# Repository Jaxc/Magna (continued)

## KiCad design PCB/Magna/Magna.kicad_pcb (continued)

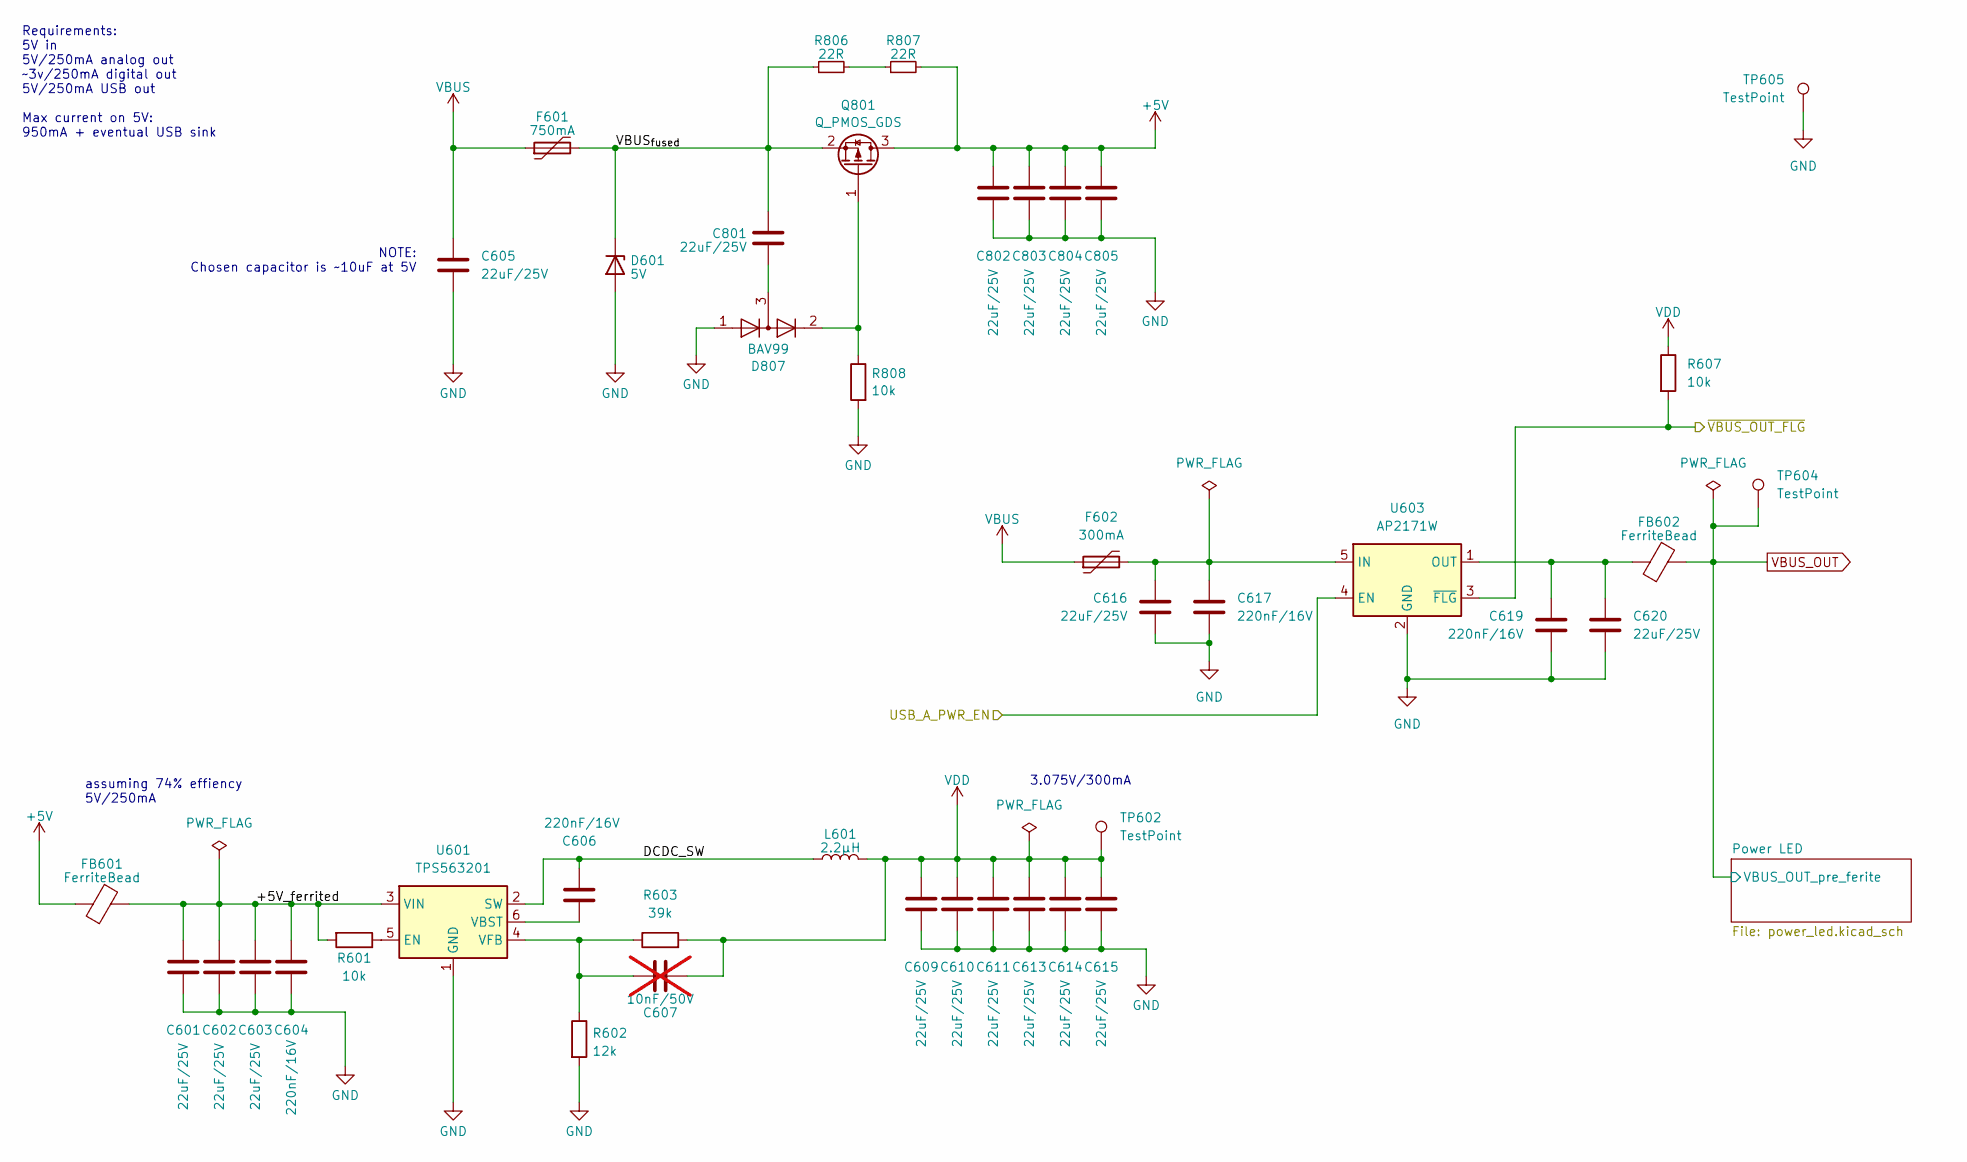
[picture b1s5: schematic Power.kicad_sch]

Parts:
C601, C602, C603, C605, C609, C610, C611, C613, C614, C615, C616, C620, C801, C802, C803, C804, C805: 22uF/25V; C_0805_2012Metric_Pad1.18x1.45mm_HandSolder; LCSC C45783
C604, C606, C617, C619: 220nF/16V; C_0402_1005Metric_Pad0.74x0.62mm_HandSolder; LCSC C16772
C607: 10nF/50V; C_0805_2012Metric_Pad1.18x1.45mm_HandSolder; LCSC C1710; not fitted
D601: 5V; D_SOD-123; LCSC C19077393
D807: BAV99; SOT-23; LCSC C2500
F601: 750mA; Fuse_2920_7451Metric_Pad2.10x5.45mm_HandSolder; LCSC C20822
F602: 300mA; Fuse_2920_7451Metric_Pad2.10x5.45mm_HandSolder; LCSC C20820
FB601, FB602: FerriteBead; L_0805_2012Metric; LCSC C1015
L601: 2.2µH; L_Sunlord_SWPA3012S; LCSC C182126
Q801: Q_PMOS_GDS; SOT-23; LCSC C15127
R601, R607, R808: 10k; R_0805_2012Metric_Pad1.20x1.40mm_HandSolder; LCSC C17414
R602: 12k; R_0805_2012Metric_Pad1.20x1.40mm_HandSolder; LCSC C17444
R603: 39k; R_0805_2012Metric_Pad1.20x1.40mm_HandSolder; LCSC C17713
R806, R807: 22R; R_0805_2012Metric_Pad1.20x1.40mm_HandSolder; LCSC C17561
TP602, TP604, TP605: TestPoint; TestPoint_Keystone_5000-5004_Miniature
U601: TPS563201; SOT-23-6; LCSC C116592
U603: AP2171W; SOT-23-5; LCSC C110466

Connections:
+5V: C802.1, C803.1, C804.1, C805.1, FB601.1, Q801.3 (D), R807.2; also elsewhere on the board
/MCU/USB_A_PWR_EN: U603.4 (EN); also elsewhere on the board
/MCU/~VBUS_OUT_FLG: R607.2, U603.3 (~FLG); also elsewhere on the board
/POWER/+5V_ferrited: C601.1, C602.1, C603.1, C604.1, FB601.2, R601.2, U601.3 (VIN)
/POWER/DCDC_SW: C606.1, L601.1, U601.2 (SW)
/POWER/VBUS_{fused}: C801.1, D601.1 (K), F601.2, Q801.2 (S), R806.1
GND: C601.2, C602.2, C603.2, C604.2, C605.2, C609.2, C610.2, C611.2, C613.2, C614.2, C615.2, C616.2, C617.2, C619.2, C620.2, C802.2, C803.2, C804.2, C805.2, D601.2 (A), D807.1 (K), R602.2, R808.2, TP605.1, U601.1 (GND), U603.2 (GND); also elsewhere on the board
unnamed: C801.2, D807.3 (K)
unnamed: D807.2 (A), Q801.1 (G), R808.1
unnamed: R806.2, R807.1
unnamed: R601.1, U601.5 (EN)
unnamed: C606.2, U601.6 (VBST)
unnamed: C607.1, R602.1, R603.1, U601.4 (VFB)
unnamed: C616.1, C617.1, F602.2, U603.5 (IN)
unnamed: C619.1, C620.1, FB602.1, U603.1 (OUT)
VBUS: C605.1, F601.1, F602.1; also elsewhere on the board
VBUS_OUT: FB602.2, TP604.1; also elsewhere on the board
VDD: C607.2, C609.1, C610.1, C611.1, C613.1, C614.1, C615.1, L601.2, R603.2, R607.1, TP602.1; also elsewhere on the board

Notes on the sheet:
NOTE: Chosen capacitor is ~10uF at 5V
3.075V/300mA
assuming 74% effiency 5V/250mA
Requirements: 5V in 5V/250mA analog out ~3v/250mA digital out 5V/250mA USB out Max current on 5V: 950mA + eventual USB sink

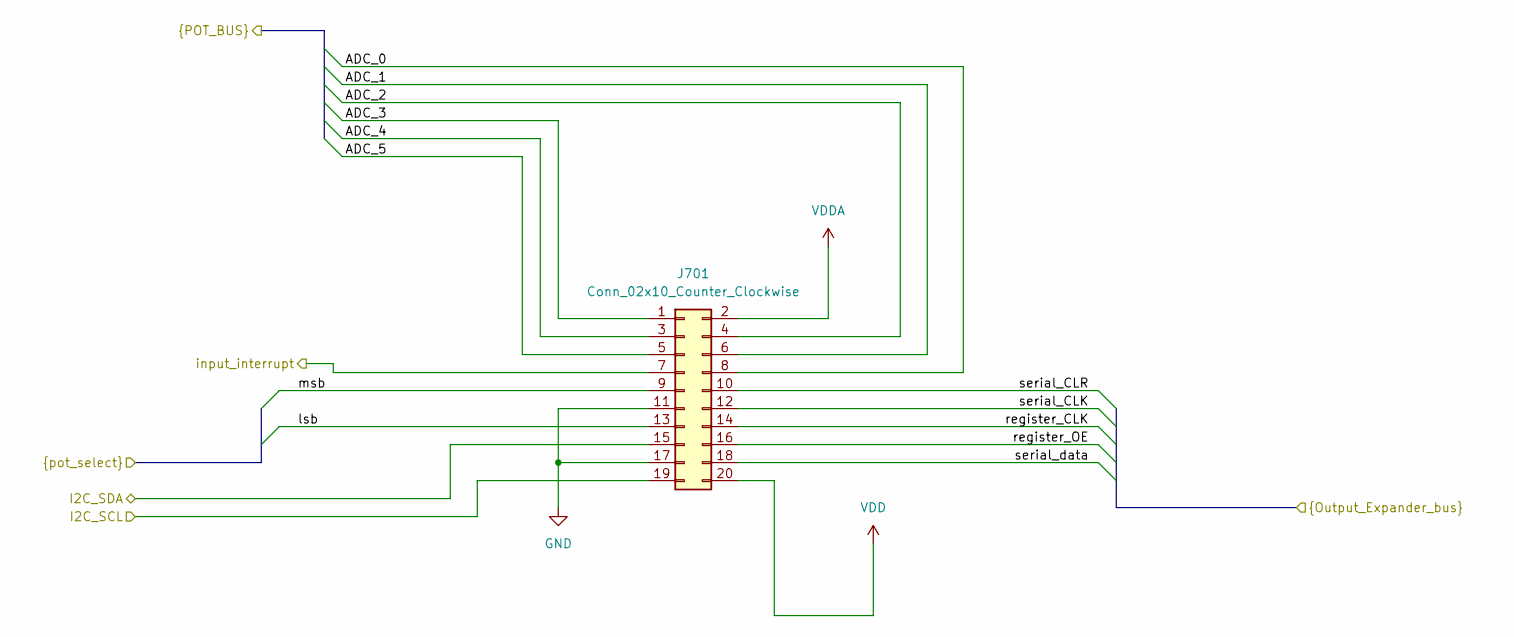
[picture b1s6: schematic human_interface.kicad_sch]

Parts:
J701: Conn_02x10_Counter_Clockwise; PinHeader_2x10_P2.54mm_Horizontal

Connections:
/Human Interface/ADC_0: J701.8; also elsewhere on the board
/Human Interface/ADC_1: J701.6; also elsewhere on the board
/Human Interface/ADC_2: J701.4; also elsewhere on the board
/Human Interface/ADC_3: J701.1; also elsewhere on the board
/Human Interface/ADC_4: J701.3; also elsewhere on the board
/Human Interface/ADC_5: J701.5; also elsewhere on the board
/Human Interface/I2C_SCL: J701.19; also elsewhere on the board
/Human Interface/I2C_SDA: J701.15; also elsewhere on the board
/Human Interface/input_interrupt: J701.7; also elsewhere on the board
/Human Interface/lsb: J701.13; also elsewhere on the board
/Human Interface/msb: J701.9; also elsewhere on the board
/Human Interface/register_CLK: J701.14; also elsewhere on the board
/Human Interface/register_OE: J701.16; also elsewhere on the board
/Human Interface/serial_CLK: J701.12; also elsewhere on the board
/Human Interface/serial_CLR: J701.10; also elsewhere on the board
/Human Interface/serial_data: J701.18; also elsewhere on the board
GND: J701.11, J701.17; also elsewhere on the board
VDD: J701.20; also elsewhere on the board
VDDA: J701.2; also elsewhere on the board

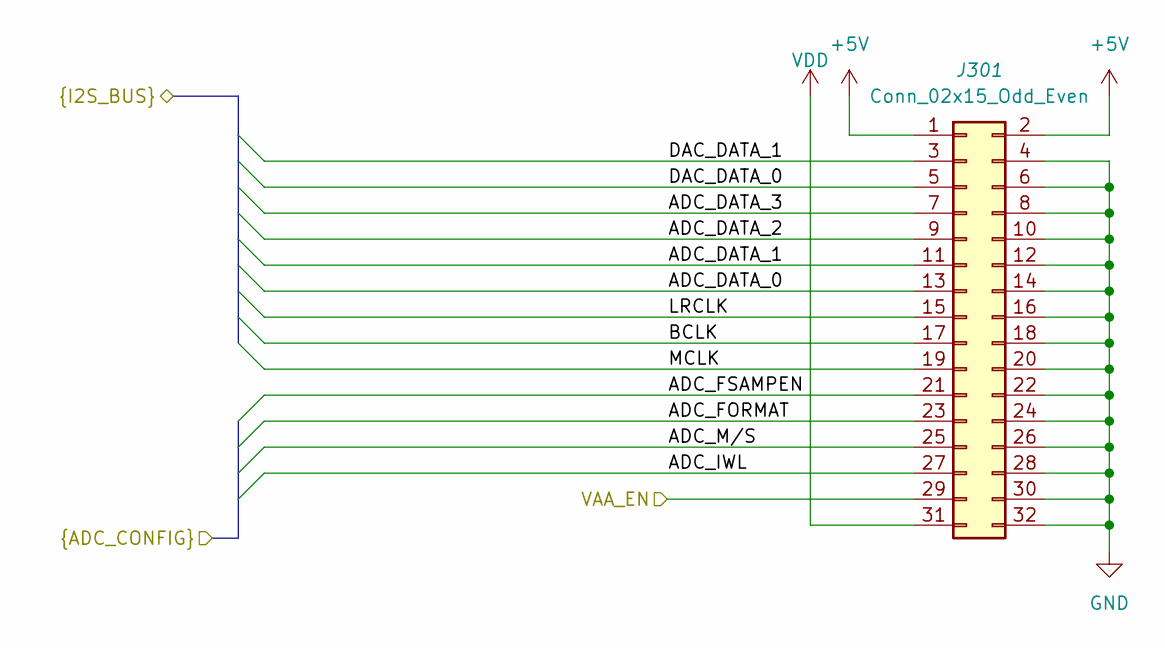
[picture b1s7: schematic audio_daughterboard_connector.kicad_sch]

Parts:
J301: Conn_02x15_Odd_Even; PinSocket_2x16_P2.54mm_Horizontal

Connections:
+5V: J301.1, J301.2; also elsewhere on the board
/Audio Daughterboard Connector/ADC_DATA_0: J301.13; also elsewhere on the board
/Audio Daughterboard Connector/ADC_DATA_1: J301.11; also elsewhere on the board
/Audio Daughterboard Connector/ADC_DATA_2: J301.9; also elsewhere on the board
/Audio Daughterboard Connector/ADC_DATA_3: J301.7; also elsewhere on the board
/Audio Daughterboard Connector/ADC_FORMAT: J301.23; also elsewhere on the board
/Audio Daughterboard Connector/ADC_FSAMPEN: J301.21; also elsewhere on the board
/Audio Daughterboard Connector/ADC_IWL: J301.27; also elsewhere on the board
/Audio Daughterboard Connector/ADC_M/S: J301.25; also elsewhere on the board
/Audio Daughterboard Connector/BCLK: J301.17; also elsewhere on the board
/Audio Daughterboard Connector/DAC_DATA_0: J301.5; also elsewhere on the board
/Audio Daughterboard Connector/DAC_DATA_1: J301.3; also elsewhere on the board
/Audio Daughterboard Connector/LRCLK: J301.15; also elsewhere on the board
/Audio Daughterboard Connector/MCLK: J301.19; also elsewhere on the board
/Audio Daughterboard Connector/VAA_EN: J301.29; also elsewhere on the board
GND: J301.4, J301.6, J301.8, J301.10, J301.12, J301.14, J301.16, J301.18, J301.20, J301.22, J301.24, J301.26, J301.28, J301.30, J301.32; also elsewhere on the board
VDD: J301.31; also elsewhere on the board

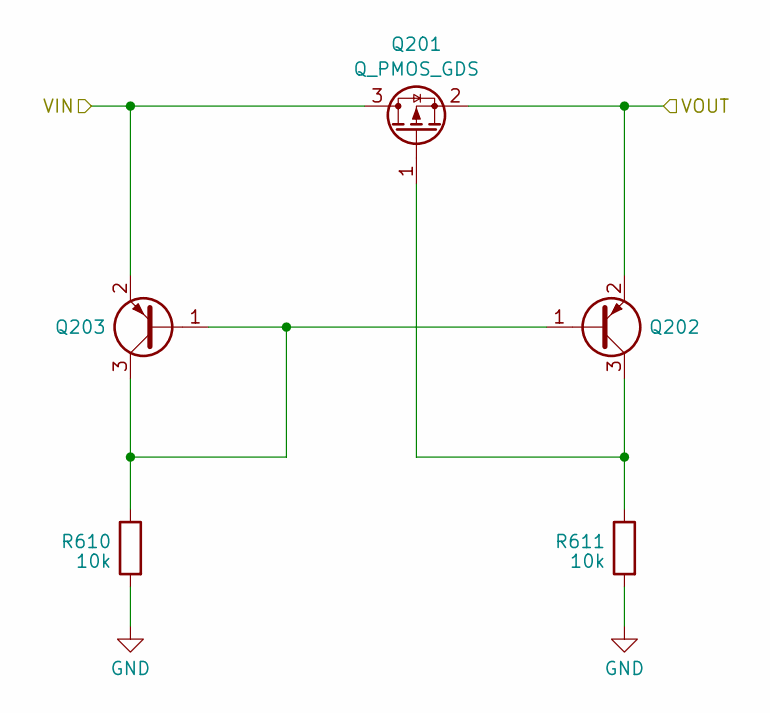
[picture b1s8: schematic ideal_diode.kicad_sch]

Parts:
Q201: Q_PMOS_GDS; SOT-23; LCSC C15127
Q202, Q203: Q_PNP_BEC; SOT-23; LCSC C8326
R610, R611: 10k; R_0805_2012Metric_Pad1.20x1.40mm_HandSolder; LCSC C17414

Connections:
/USB/USB_B_VBUS: Q201.3 (D), Q203.2 (E); also elsewhere on the board
GND: R610.2, R611.2; also elsewhere on the board
unnamed: Q201.1 (G), Q202.3 (C), R611.1
unnamed: Q202.1 (B), Q203.1 (B), Q203.3 (C), R610.1
VBUS: Q201.2 (S), Q202.2 (E); also elsewhere on the board

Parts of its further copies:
Q701: Q_PMOS_GDS; SOT-23; LCSC C15127
Q702, Q703: Q_PNP_BEC; SOT-23; LCSC C8326
R608, R609: 10k; R_0805_2012Metric_Pad1.20x1.40mm_HandSolder; LCSC C17414

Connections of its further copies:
/USB/USB_C_VBUS: Q701.3 (D), Q703.2 (E); also elsewhere on the board
GND: R608.2, R609.2; also elsewhere on the board
unnamed: Q701.1 (G), Q702.3 (C), R609.1
unnamed: Q702.1 (B), Q703.1 (B), Q703.3 (C), R608.1
VBUS: Q701.2 (S), Q702.2 (E); also elsewhere on the board

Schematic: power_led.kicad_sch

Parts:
D801, D802, D803, D804, D805: Red; D_0805_2012Metric_Pad1.15x1.40mm_HandSolder; LCSC C84256
R801, R802, R803: 680R; R_0805_2012Metric_Pad1.20x1.40mm_HandSolder; LCSC C17798
R804, R805: 220R; R_0805_2012Metric_Pad1.20x1.40mm_HandSolder; LCSC C17557

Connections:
+5V: R803.1; also elsewhere on the board
GND: D801.1 (K), D802.1 (K), D803.1 (K), D804.1 (K), D805.1 (K); also elsewhere on the board
unnamed: D801.2 (A), R801.2
unnamed: D802.2 (A), R802.2
unnamed: D803.2 (A), R803.2
unnamed: D804.2 (A), R804.2
unnamed: D805.2 (A), R805.2
VBUS: R802.1; also elsewhere on the board
VBUS_OUT: R801.1; also elsewhere on the board
VDD: R804.1; also elsewhere on the board
VDDA: R805.1; also elsewhere on the board

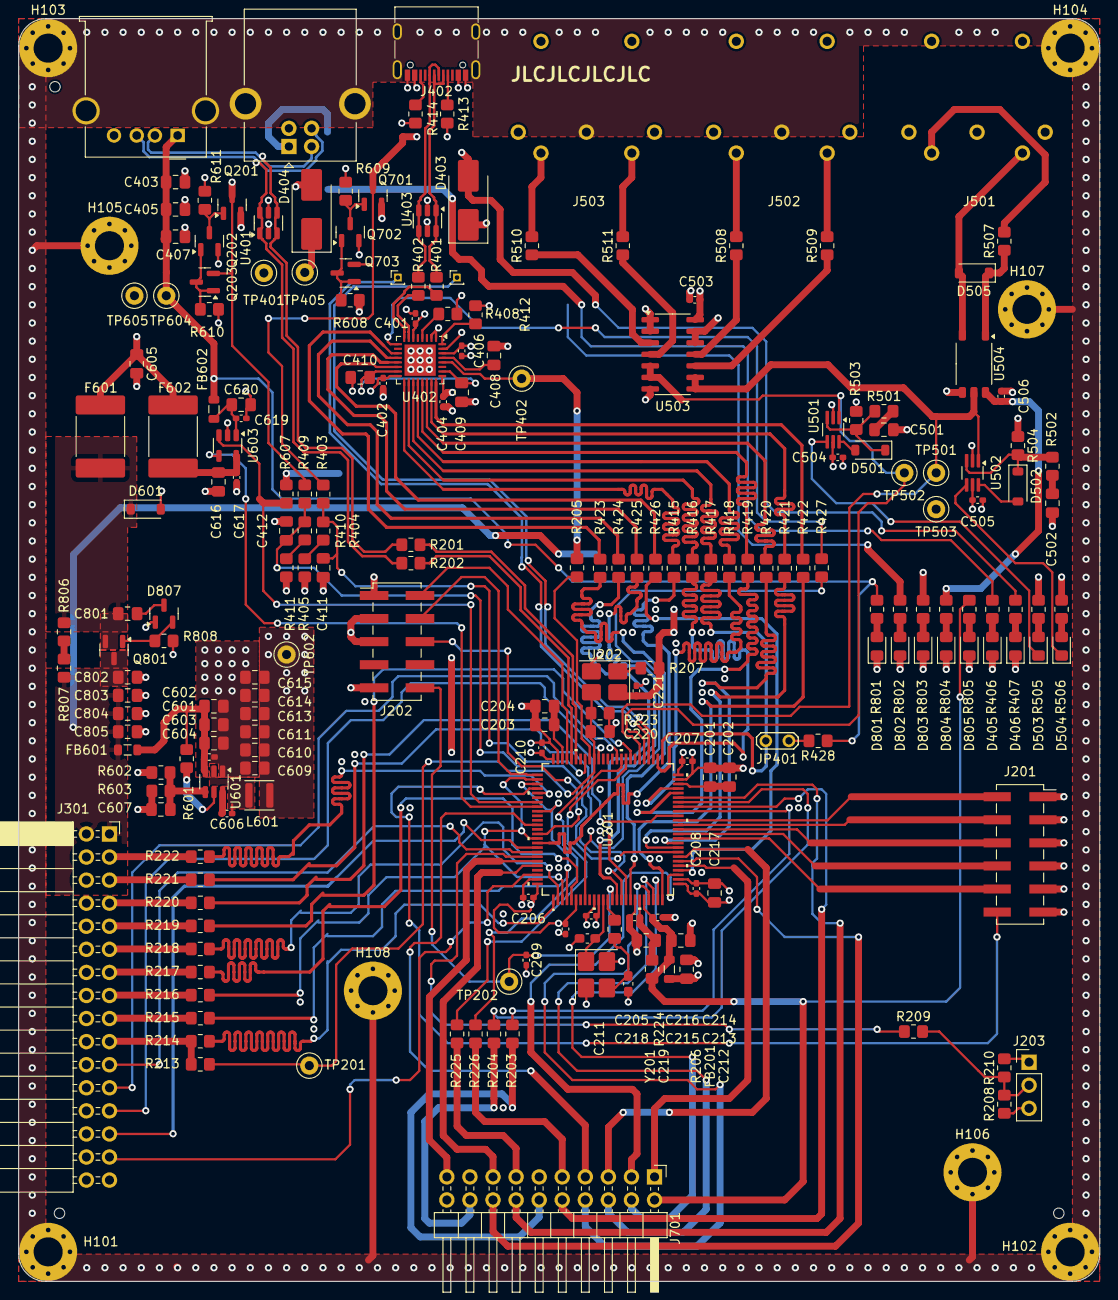
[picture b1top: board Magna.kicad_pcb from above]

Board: 4 copper layers, 119.0 x 139.0 mm, 217 parts (0 on the bottom side), 168 nets.

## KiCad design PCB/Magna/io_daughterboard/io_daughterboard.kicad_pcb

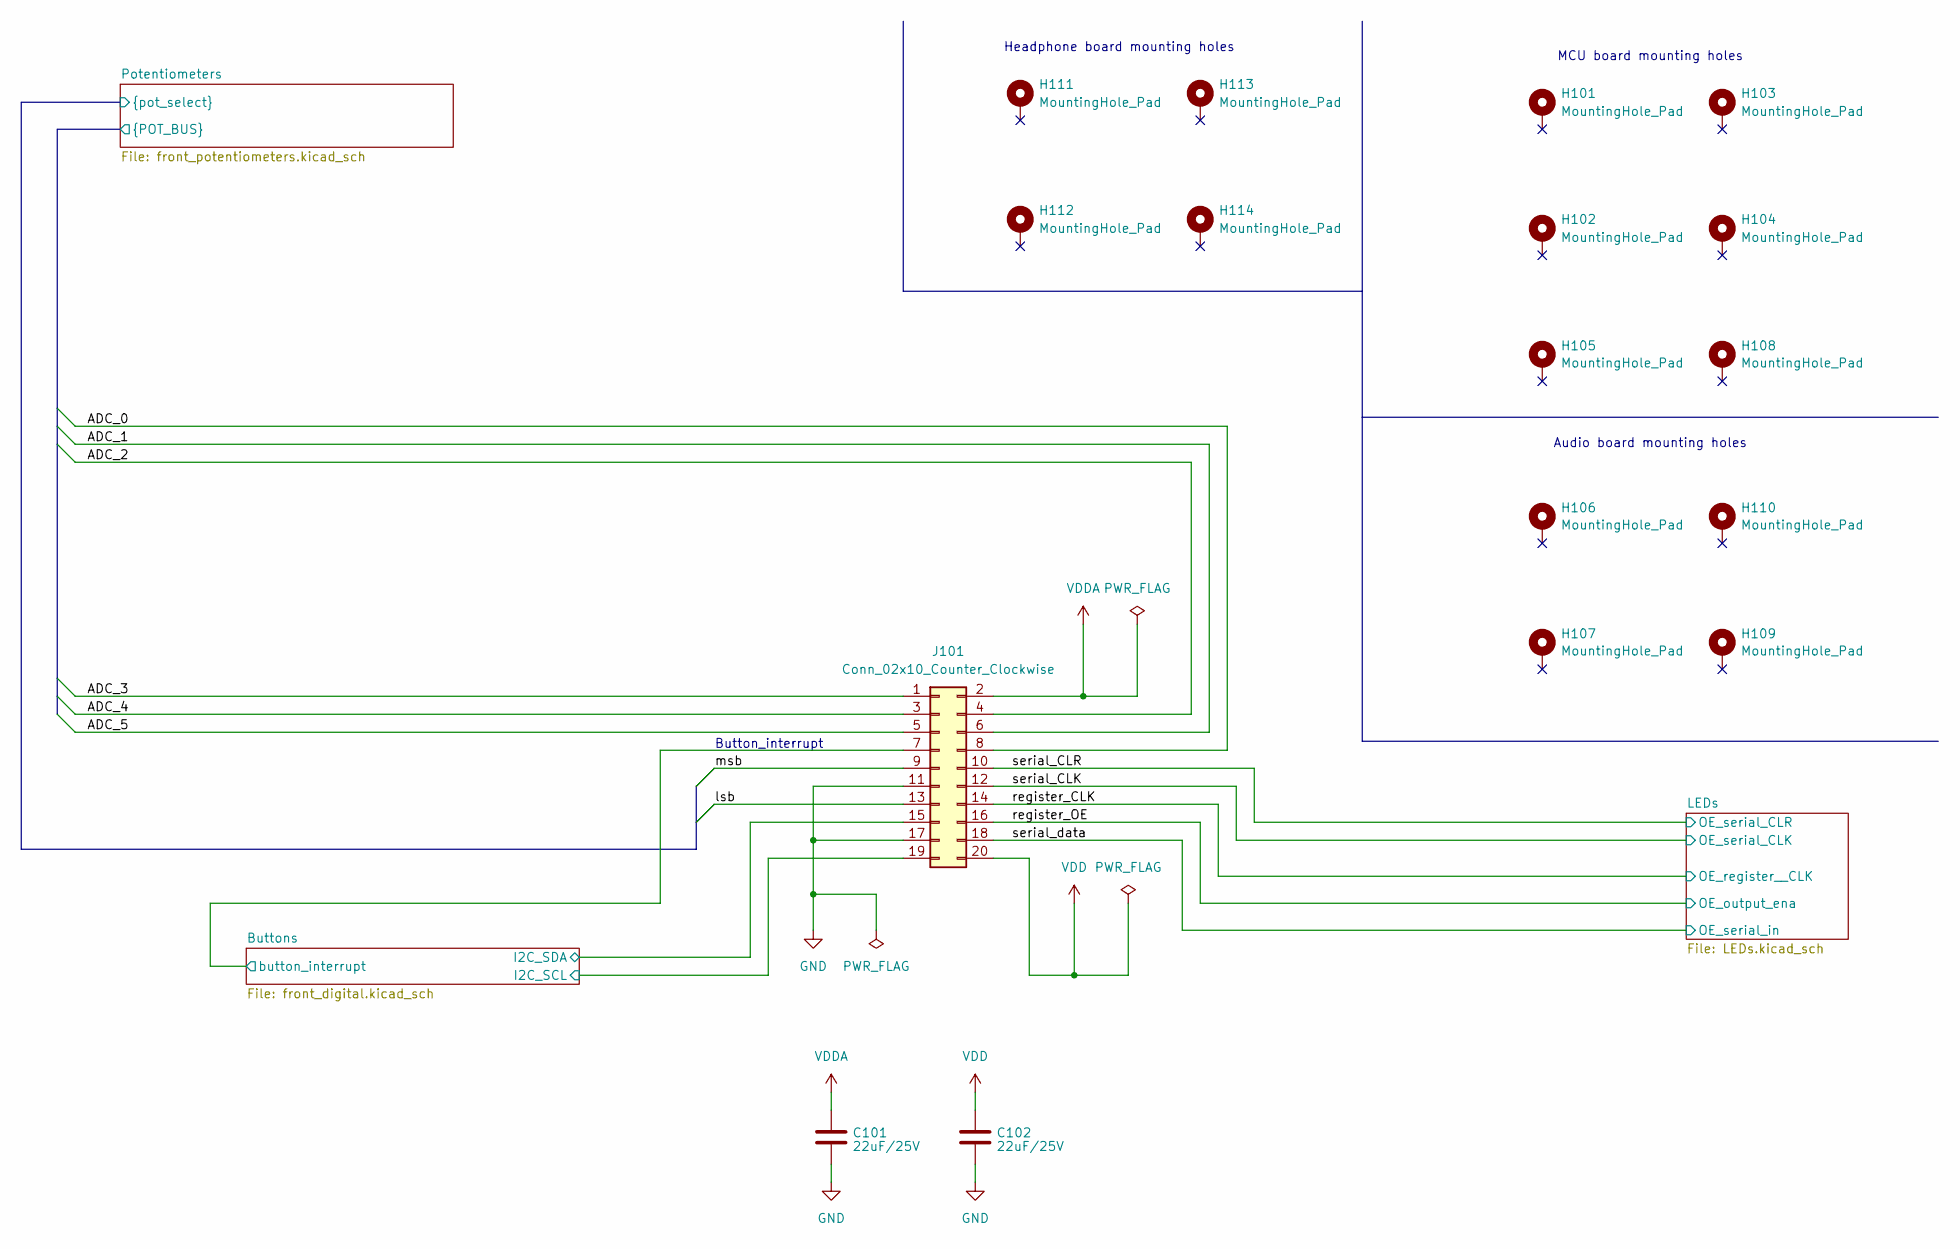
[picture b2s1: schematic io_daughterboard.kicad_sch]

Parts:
C101, C102: 22uF/25V; C_0805_2012Metric_Pad1.18x1.45mm_HandSolder; LCSC C45783
H101, H102, H103, H104, H105, H106, H107, H108, H109, H110, H111, H112, H113, H114: MountingHole_Pad; MountingHole_3.2mm_M3_Pad_Via
J101: Conn_02x10_Counter_Clockwise; PinSocket_2x10_P2.54mm_Vertical

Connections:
/Buttons/I2C_SCL: J101.19; also elsewhere on the board
/Buttons/I2C_SDA: J101.15; also elsewhere on the board
/Buttons/button_interrupt: J101.7; also elsewhere on the board
/Potentiometers/ADC_0: J101.8; also elsewhere on the board
/Potentiometers/ADC_1: J101.6; also elsewhere on the board
/Potentiometers/ADC_2: J101.4; also elsewhere on the board
/Potentiometers/ADC_3: J101.1; also elsewhere on the board
/Potentiometers/ADC_4: J101.3; also elsewhere on the board
/Potentiometers/ADC_5: J101.5; also elsewhere on the board
/Potentiometers/lsb: J101.13; also elsewhere on the board
/Potentiometers/msb: J101.9; also elsewhere on the board
/register_CLK: J101.14; also elsewhere on the board
/register_OE: J101.16; also elsewhere on the board
/serial_CLK: J101.12; also elsewhere on the board
/serial_CLR: J101.10; also elsewhere on the board
/serial_data: J101.18; also elsewhere on the board
GND: C101.2, C102.2, J101.11, J101.17; also elsewhere on the board
VDD: C102.1, J101.20; also elsewhere on the board
VDDA: C101.1, J101.2; also elsewhere on the board

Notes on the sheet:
Audio board mounting holes
MCU board mounting holes
Button_interrupt
Headphone board mounting holes

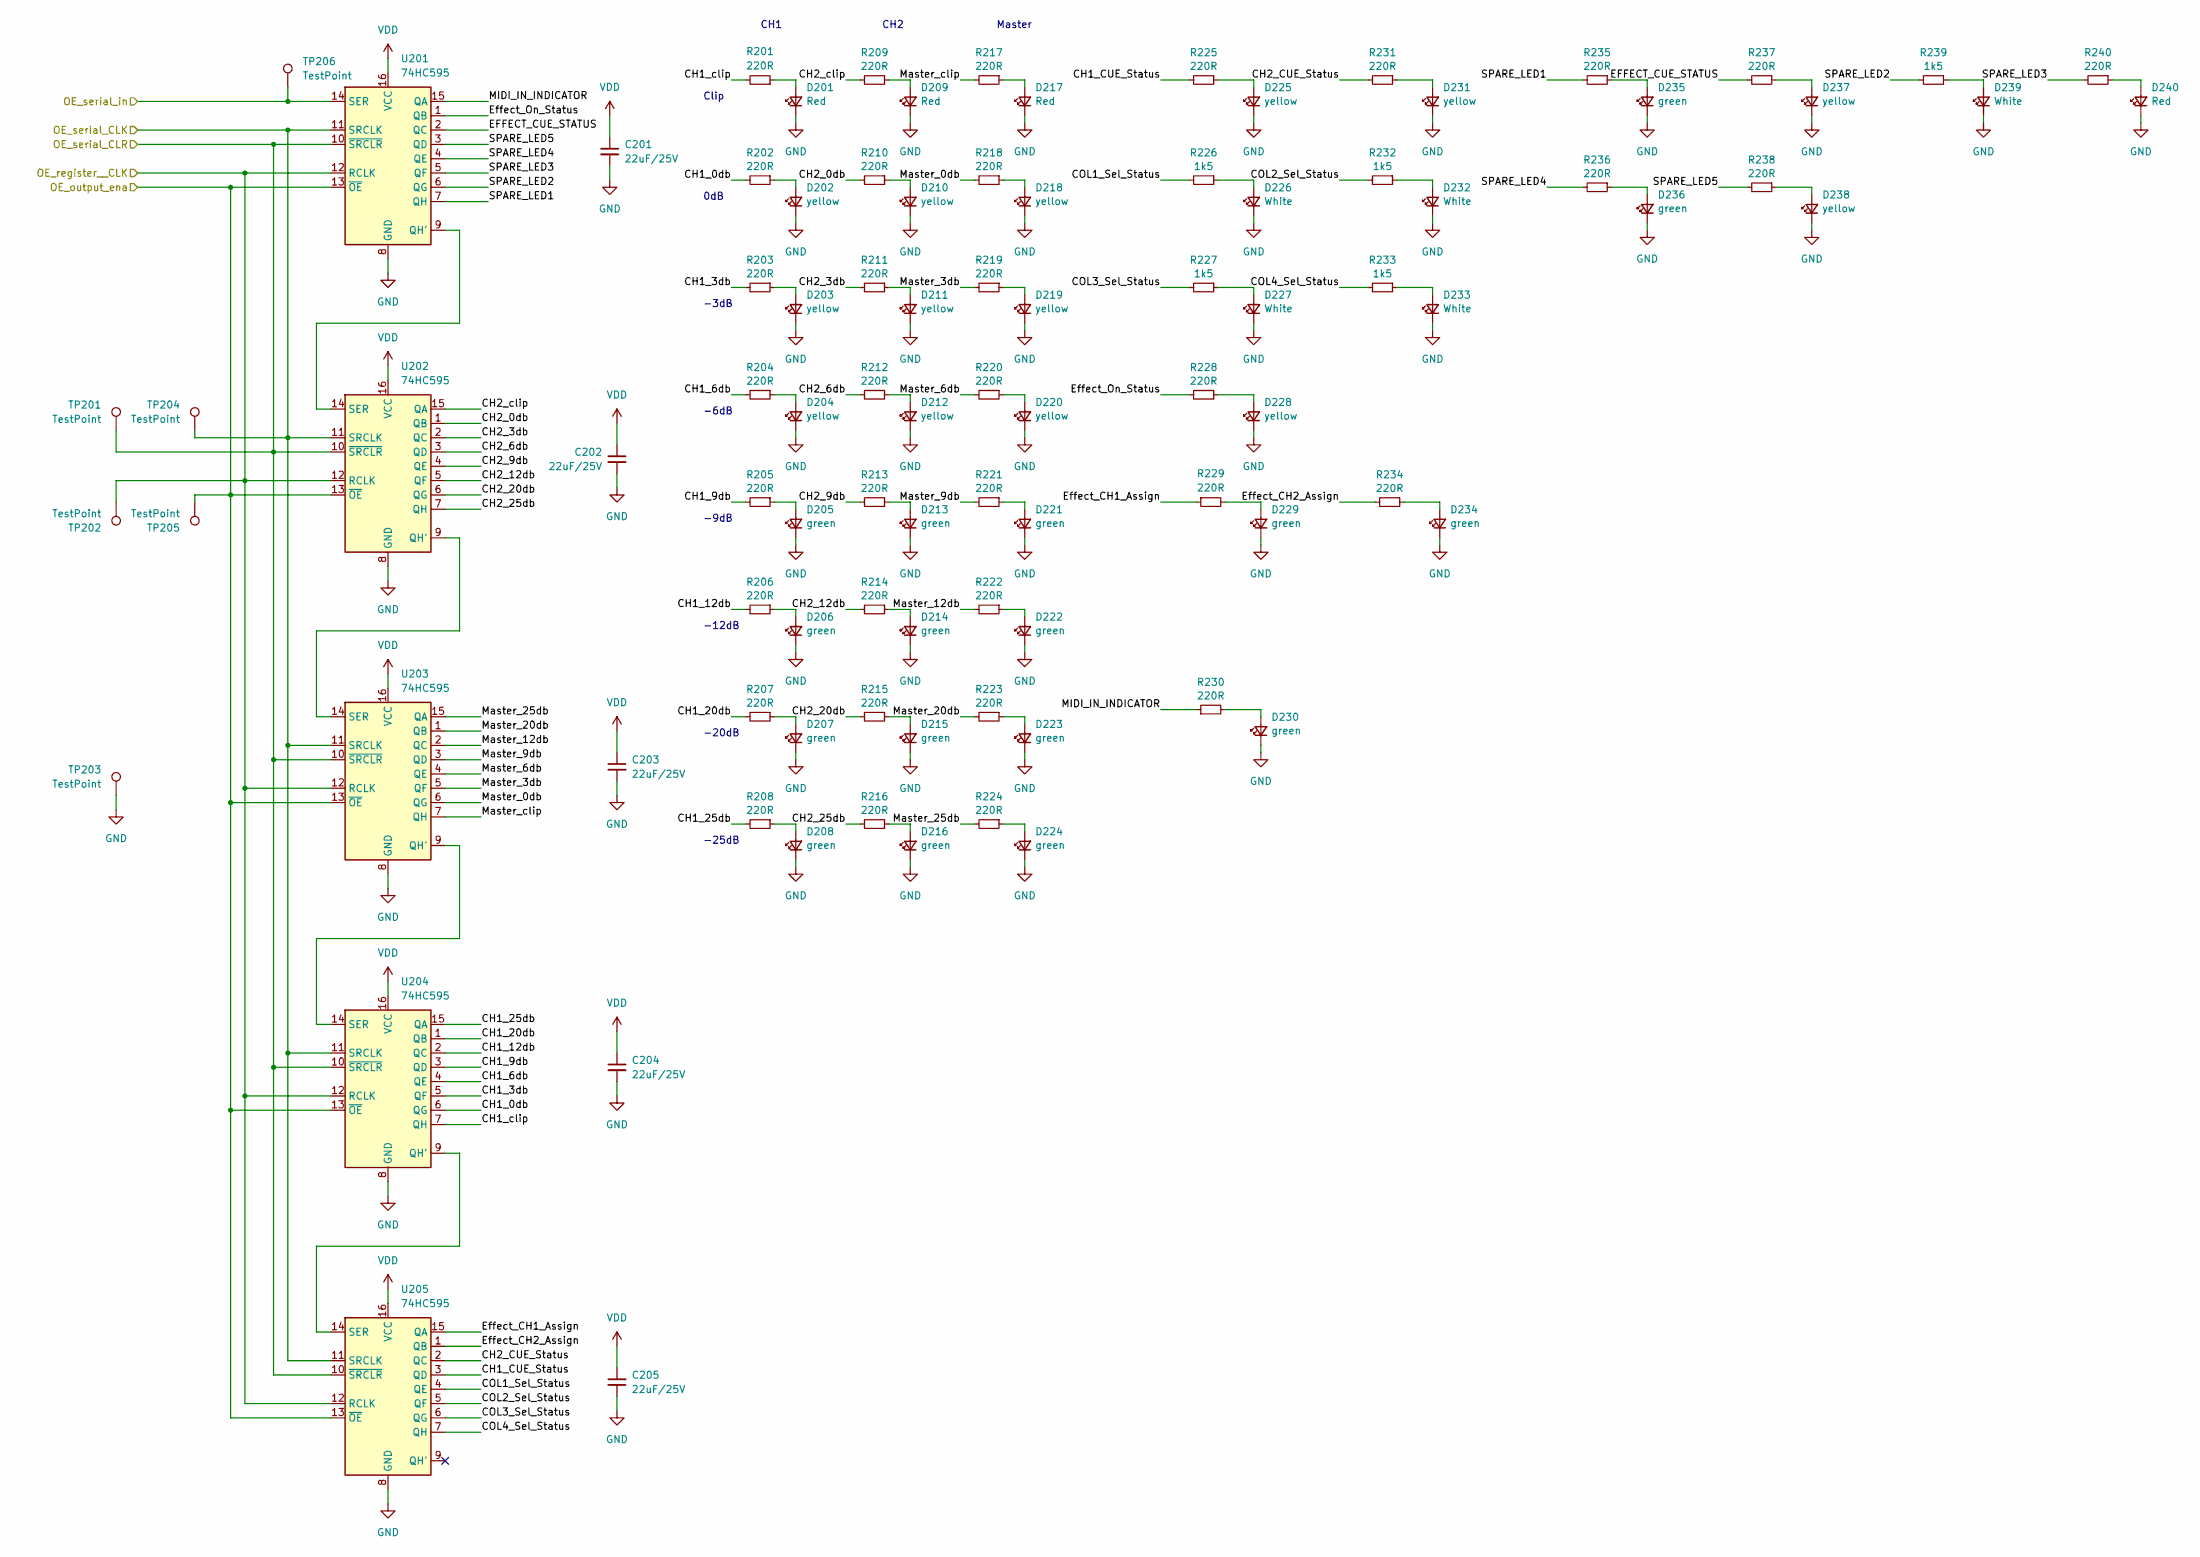
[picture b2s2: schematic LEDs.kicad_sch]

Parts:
C201, C202, C203, C204, C205: 22uF/25V; C_0805_2012Metric_Pad1.18x1.45mm_HandSolder; LCSC C45783
D201, D209, D217, D240: Red; D_0805_2012Metric_Pad1.15x1.40mm_HandSolder; LCSC C84256
D202, D203, D204, D210, D211, D212, D218, D219, D220, D225, D228, D231, D237, D238: yellow; D_0805_2012Metric_Pad1.15x1.40mm_HandSolder; LCSC C2296
D205, D206, D207, D208, D213, D214, D215, D216, D221, D222, D223, D224, D229, D230, D234, D235, D236: green; D_0805_2012Metric_Pad1.15x1.40mm_HandSolder; LCSC C2297
D226, D227, D232, D233, D239: White; D_0805_2012Metric_Pad1.15x1.40mm_HandSolder; LCSC C34499
R201, R202, R203, R204, R205, R206, R207, R208, R209, R210, R211, R212, R213, R214, R215, R216, R217, R218, R219, R220, R221, R222, R223, R224, R225, R228, R229, R230, R231, R234, R235, R236, R237, R238, R240: 220R; R_0805_2012Metric_Pad1.20x1.40mm_HandSolder; LCSC C17557
R226, R227, R232, R233, R239: 1k5; R_0805_2012Metric_Pad1.20x1.40mm_HandSolder; LCSC C4310
TP201, TP202, TP203, TP204, TP205, TP206: TestPoint; TestPoint_Keystone_5000-5004_Miniature
U201, U202, U203, U204, U205: 74HC595; SO-16_3.9x9.9mm_P1.27mm; LCSC C93838

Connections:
/LEDs/CH1_0db: R202.2, U204.6 (QG)
/LEDs/CH1_3db: R203.2, U204.5 (QF)
/LEDs/CH1_6db: R204.2, U204.4 (QE)
/LEDs/CH1_9db: R205.2, U204.3 (QD)
/LEDs/CH1_12db: R206.2, U204.2 (QC)
/LEDs/CH1_20db: R207.2, U204.1 (QB)
/LEDs/CH1_25db: R208.2, U204.15 (QA)
/LEDs/CH1_CUE_Status: R225.2, U205.3 (QD)
/LEDs/CH1_clip: R201.2, U204.7 (QH)
/LEDs/CH2_0db: R210.2, U202.1 (QB)
/LEDs/CH2_3db: R211.2, U202.2 (QC)
/LEDs/CH2_6db: R212.2, U202.3 (QD)
/LEDs/CH2_9db: R213.2, U202.4 (QE)
/LEDs/CH2_12db: R214.2, U202.5 (QF)
/LEDs/CH2_20db: R215.2, U202.6 (QG)
/LEDs/CH2_25db: R216.2, U202.7 (QH)
/LEDs/CH2_CUE_Status: R231.2, U205.2 (QC)
/LEDs/CH2_clip: R209.2, U202.15 (QA)
/LEDs/COL1_Sel_Status: R226.2, U205.4 (QE)
/LEDs/COL2_Sel_Status: R232.2, U205.5 (QF)
/LEDs/COL3_Sel_Status: R227.2, U205.6 (QG)
/LEDs/COL4_Sel_Status: R233.2, U205.7 (QH)
/LEDs/EFFECT_CUE_STATUS: R237.2, U201.2 (QC)
/LEDs/Effect_CH1_Assign: R229.1, U205.15 (QA)
/LEDs/Effect_CH2_Assign: R234.2, U205.1 (QB)
/LEDs/Effect_On_Status: R228.2, U201.1 (QB)
/LEDs/MIDI_IN_INDICATOR: R230.1, U201.15 (QA)
/LEDs/Master_0db: R218.2, U203.6 (QG)
/LEDs/Master_3db: R219.2, U203.5 (QF)
/LEDs/Master_6db: R220.2, U203.4 (QE)
/LEDs/Master_9db: R221.2, U203.3 (QD)
/LEDs/Master_12db: R222.2, U203.2 (QC)
/LEDs/Master_20db: R223.2, U203.1 (QB)
/LEDs/Master_25db: R224.2, U203.15 (QA)
/LEDs/Master_clip: R217.2, U203.7 (QH)
/LEDs/SPARE_LED1: R235.2, U201.7 (QH)
/LEDs/SPARE_LED2: R239.2, U201.6 (QG)
/LEDs/SPARE_LED3: R240.2, U201.5 (QF)
/LEDs/SPARE_LED4: R236.2, U201.4 (QE)
/LEDs/SPARE_LED5: R238.2, U201.3 (QD)
/register_CLK: TP202.1, U201.12 (RCLK), U202.12 (RCLK), U203.12 (RCLK), U204.12 (RCLK), U205.12 (RCLK); also elsewhere on the board
/register_OE: TP205.1, U201.13 (~OE), U202.13 (~OE), U203.13 (~OE), U204.13 (~OE), U205.13 (~OE); also elsewhere on the board
/serial_CLK: TP204.1, U201.11 (SRCLK), U202.11 (SRCLK), U203.11 (SRCLK), U204.11 (SRCLK), U205.11 (SRCLK); also elsewhere on the board
/serial_CLR: TP201.1, U201.10 (~SRCLR), U202.10 (~SRCLR), U203.10 (~SRCLR), U204.10 (~SRCLR), U205.10 (~SRCLR); also elsewhere on the board
/serial_data: TP206.1, U201.14 (SER); also elsewhere on the board
GND: C201.2, C202.2, C203.2, C204.2, C205.2, D201.1 (K), D202.1 (K), D203.1 (K), D204.1 (K), D205.1 (K), D206.1 (K), D207.1 (K), D208.1 (K), D209.1 (K), D210.1 (K), D211.1 (K), D212.1 (K), D213.1 (K), D214.1 (K), D215.1 (K), D216.1 (K), D217.1 (K), D218.1 (K), D219.1 (K), D220.1 (K), D221.1 (K), D222.1 (K), D223.1 (K), D224.1 (K), D225.1 (K), D226.1 (K), D227.1 (K), D228.1 (K), D229.1 (K), D230.1 (K), D231.1 (K), D232.1 (K), D233.1 (K), D234.1 (K), D235.1 (K), D236.1 (K), D237.1 (K), D238.1 (K), D239.1 (K), D240.1 (K), TP203.1, U201.8 (GND), U202.8 (GND), U203.8 (GND), U204.8 (GND), U205.8 (GND); also elsewhere on the board
unnamed: D201.2 (A), R201.1
unnamed: D202.2 (A), R202.1
unnamed: D203.2 (A), R203.1
unnamed: D204.2 (A), R204.1
unnamed: D205.2 (A), R205.1
unnamed: D206.2 (A), R206.1
unnamed: D207.2 (A), R207.1
unnamed: D208.2 (A), R208.1
unnamed: D209.2 (A), R209.1
unnamed: D210.2 (A), R210.1
unnamed: D211.2 (A), R211.1
unnamed: D212.2 (A), R212.1
unnamed: D213.2 (A), R213.1
unnamed: D214.2 (A), R214.1
unnamed: D215.2 (A), R215.1
unnamed: D216.2 (A), R216.1
unnamed: D217.2 (A), R217.1
unnamed: D218.2 (A), R218.1
unnamed: D219.2 (A), R219.1
unnamed: D220.2 (A), R220.1
unnamed: D221.2 (A), R221.1
unnamed: D222.2 (A), R222.1
unnamed: D223.2 (A), R223.1
unnamed: D224.2 (A), R224.1
unnamed: D225.2 (A), R225.1
unnamed: D226.2 (A), R226.1
unnamed: D227.2 (A), R227.1
unnamed: D228.2 (A), R228.1
unnamed: D229.2 (A), R229.2
unnamed: D230.2 (A), R230.2
unnamed: D231.2 (A), R231.1
unnamed: D232.2 (A), R232.1
unnamed: D233.2 (A), R233.1
unnamed: D234.2 (A), R234.1
unnamed: D235.2 (A), R235.1
unnamed: D236.2 (A), R236.1
unnamed: D237.2 (A), R237.1
unnamed: D238.2 (A), R238.1
unnamed: D239.2 (A), R239.1
unnamed: D240.2 (A), R240.1
unnamed: U201.9 (QH'), U202.14 (SER)
unnamed: U202.9 (QH'), U203.14 (SER)
unnamed: U203.9 (QH'), U204.14 (SER)
unnamed: U204.9 (QH'), U205.14 (SER)
VDD: C201.1, C202.1, C203.1, C204.1, C205.1, U201.16 (VCC), U202.16 (VCC), U203.16 (VCC), U204.16 (VCC), U205.16 (VCC); also elsewhere on the board

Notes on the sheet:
-12dB
-6dB
-9dB
Master
0dB
-20dB
-3dB
CH1
-25dB
Clip
CH2
